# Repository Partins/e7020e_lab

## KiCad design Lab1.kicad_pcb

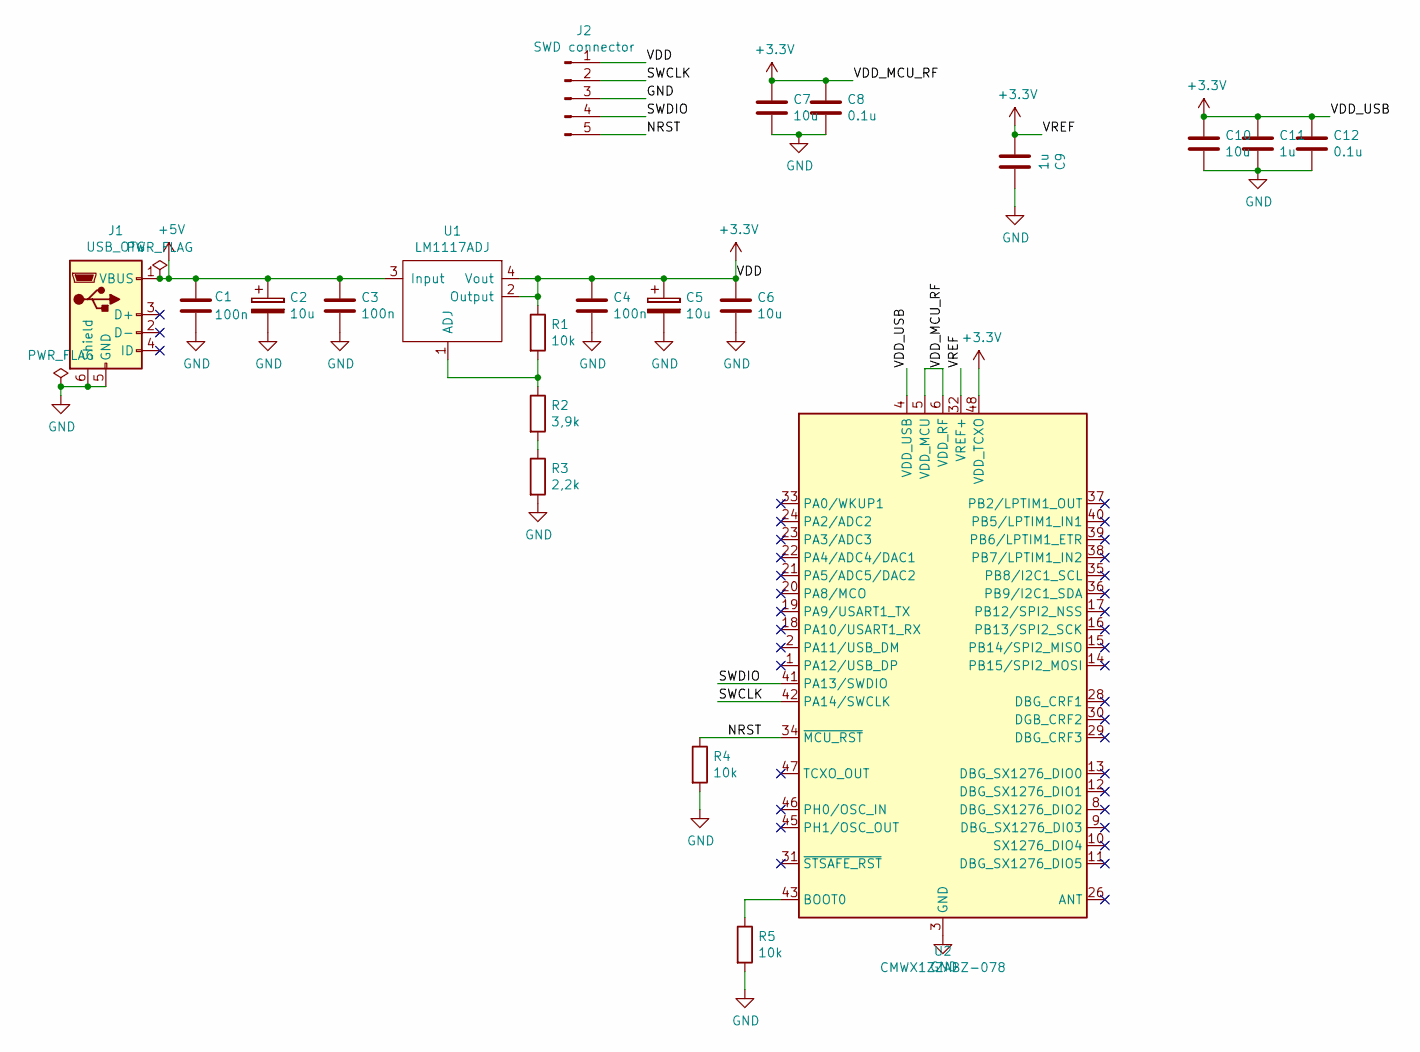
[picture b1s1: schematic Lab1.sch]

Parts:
C1, C3, C4: 100n; C_0805_2012Metric_Pad1.15x1.40mm_HandSolder
C2, C5: 10u; CP_EIA-3528-21_Kemet-B_Pad1.50x2.35mm_HandSolder
C6, C7, C10: 10u; C_0805_2012Metric_Pad1.15x1.40mm_HandSolder
C8, C12: 0.1u; C_0805_2012Metric_Pad1.15x1.40mm_HandSolder
C9, C11: 1u; C_0805_2012Metric_Pad1.15x1.40mm_HandSolder
J1: USB_OTG; USB_Micro-B_Wuerth_629105150521
J2: SWD connector; PinSocket_1x05_P2.54mm_Vertical
R1, R4, R5: 10k; R_0805_2012Metric_Pad1.15x1.40mm_HandSolder
R2: 3,9k; R_0805_2012Metric_Pad1.15x1.40mm_HandSolder
R3: 2,2k; R_0805_2012Metric_Pad1.15x1.40mm_HandSolder
U1: LM1117ADJ; SOT-223
U2: CMWX1ZZABZ-078; CMWX1ZZABZ

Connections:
+3V3: C4.2, C5.1, C6.2, C7.1, C8.1, C9.2, C10.1, C11.1, C12.1, J2.1, R1.1, U1.2 (Output), U1.4 (Vout), U2.4 (VDD_USB), U2.5 (VDD_MCU), U2.6 (VDD_RF), U2.32 (VREF+), U2.48 (VDD_TCXO)
+5V: C1.2, C2.1, C3.2, J1.1 (VBUS), U1.3 (Input)
/NRST: J2.5, R4.1, U2.34 (~MCU_RST)
/SWCLK: J2.2, U2.42 (PA14/SWCLK)
/SWDIO: J2.4, U2.41 (PA13/SWDIO)
GND: C1.1, C2.2, C3.1, C4.1, C5.2, C6.1, C7.2, C8.2, C9.1, C10.2, C11.2, C12.2, J1.5 (GND), J1.6 (Shield), J2.3, R3.2, R4.2, R5.2, U2.3 (GND), U2.7 (GND), U2.25 (GND), U2.27 (GND), U2.44 (GND), U2.49 (GND), U2.50 (GND), U2.51 (GND), U2.52 (GND), U2.53 (GND), U2.54 (GND), U2.55 (GND), U2.56 (GND), U2.57 (GND)
unnamed: R1.2, R2.1, U1.1 (ADJ)
unnamed: R2.2, R3.1
unnamed: R5.1, U2.43 (BOOT0)

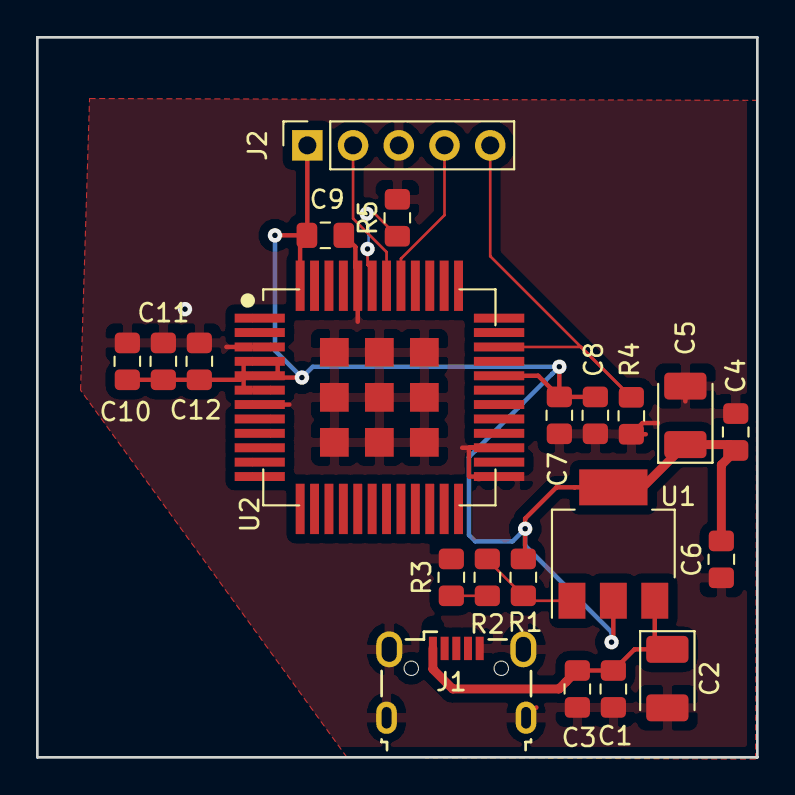
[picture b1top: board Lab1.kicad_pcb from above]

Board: 2 copper layers, 40.0 x 40.0 mm, 21 parts (0 on the bottom side), 9 nets.

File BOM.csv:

"Id";"Designator";"Package";"Quantity";"Designation";"Supplier and ref";
1;"C1,C3,C4";"C_0805_2012Metric_Pad1.15x1.40mm_HandSolder";3;"100n";;;
2;"C2,C5";"CP_EIA-3528-21_Kemet-B_Pad1.50x2.35mm_HandSolder";2;"10u";;;
3;"C6,C7,C10";"C_0805_2012Metric_Pad1.15x1.40mm_HandSolder";3;"10u";;;
4;"C8,C12";"C_0805_2012Metric_Pad1.15x1.40mm_HandSolder";2;"0.1u";;;
5;"C9,C11";"C_0805_2012Metric_Pad1.15x1.40mm_HandSolder";2;"1u";;;
6;"J1";"USB_Micro-B_Wuerth_629105150521";1;"USB_OTG";;;
7;"J2";"PinSocket_1x05_P2.54mm_Vertical";1;"SWD connector";;;
8;"R1,R4,R5";"R_0805_2012Metric_Pad1.15x1.40mm_HandSolder";3;"10k";;;
9;"R2";"R_0805_2012Metric_Pad1.15x1.40mm_HandSolder";1;"3,9k";;;
10;"R3";"R_0805_2012Metric_Pad1.15x1.40mm_HandSolder";1;"2,2k";;;
11;"U1";"SOT-223";1;"LM1117ADJ";;;
12;"U2";"CMWX1ZZABZ_longer_pads";1;"CMWX1ZZABZ-078";;;

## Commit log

2020-01-28 Initial commit. Beginning och lab2 layout
2020-01-28 Finished Lab2 Layout
2020-02-03 Added programming repo thingies for lab 3
2020-02-03 Some fixes
2020-02-03 Fixes
